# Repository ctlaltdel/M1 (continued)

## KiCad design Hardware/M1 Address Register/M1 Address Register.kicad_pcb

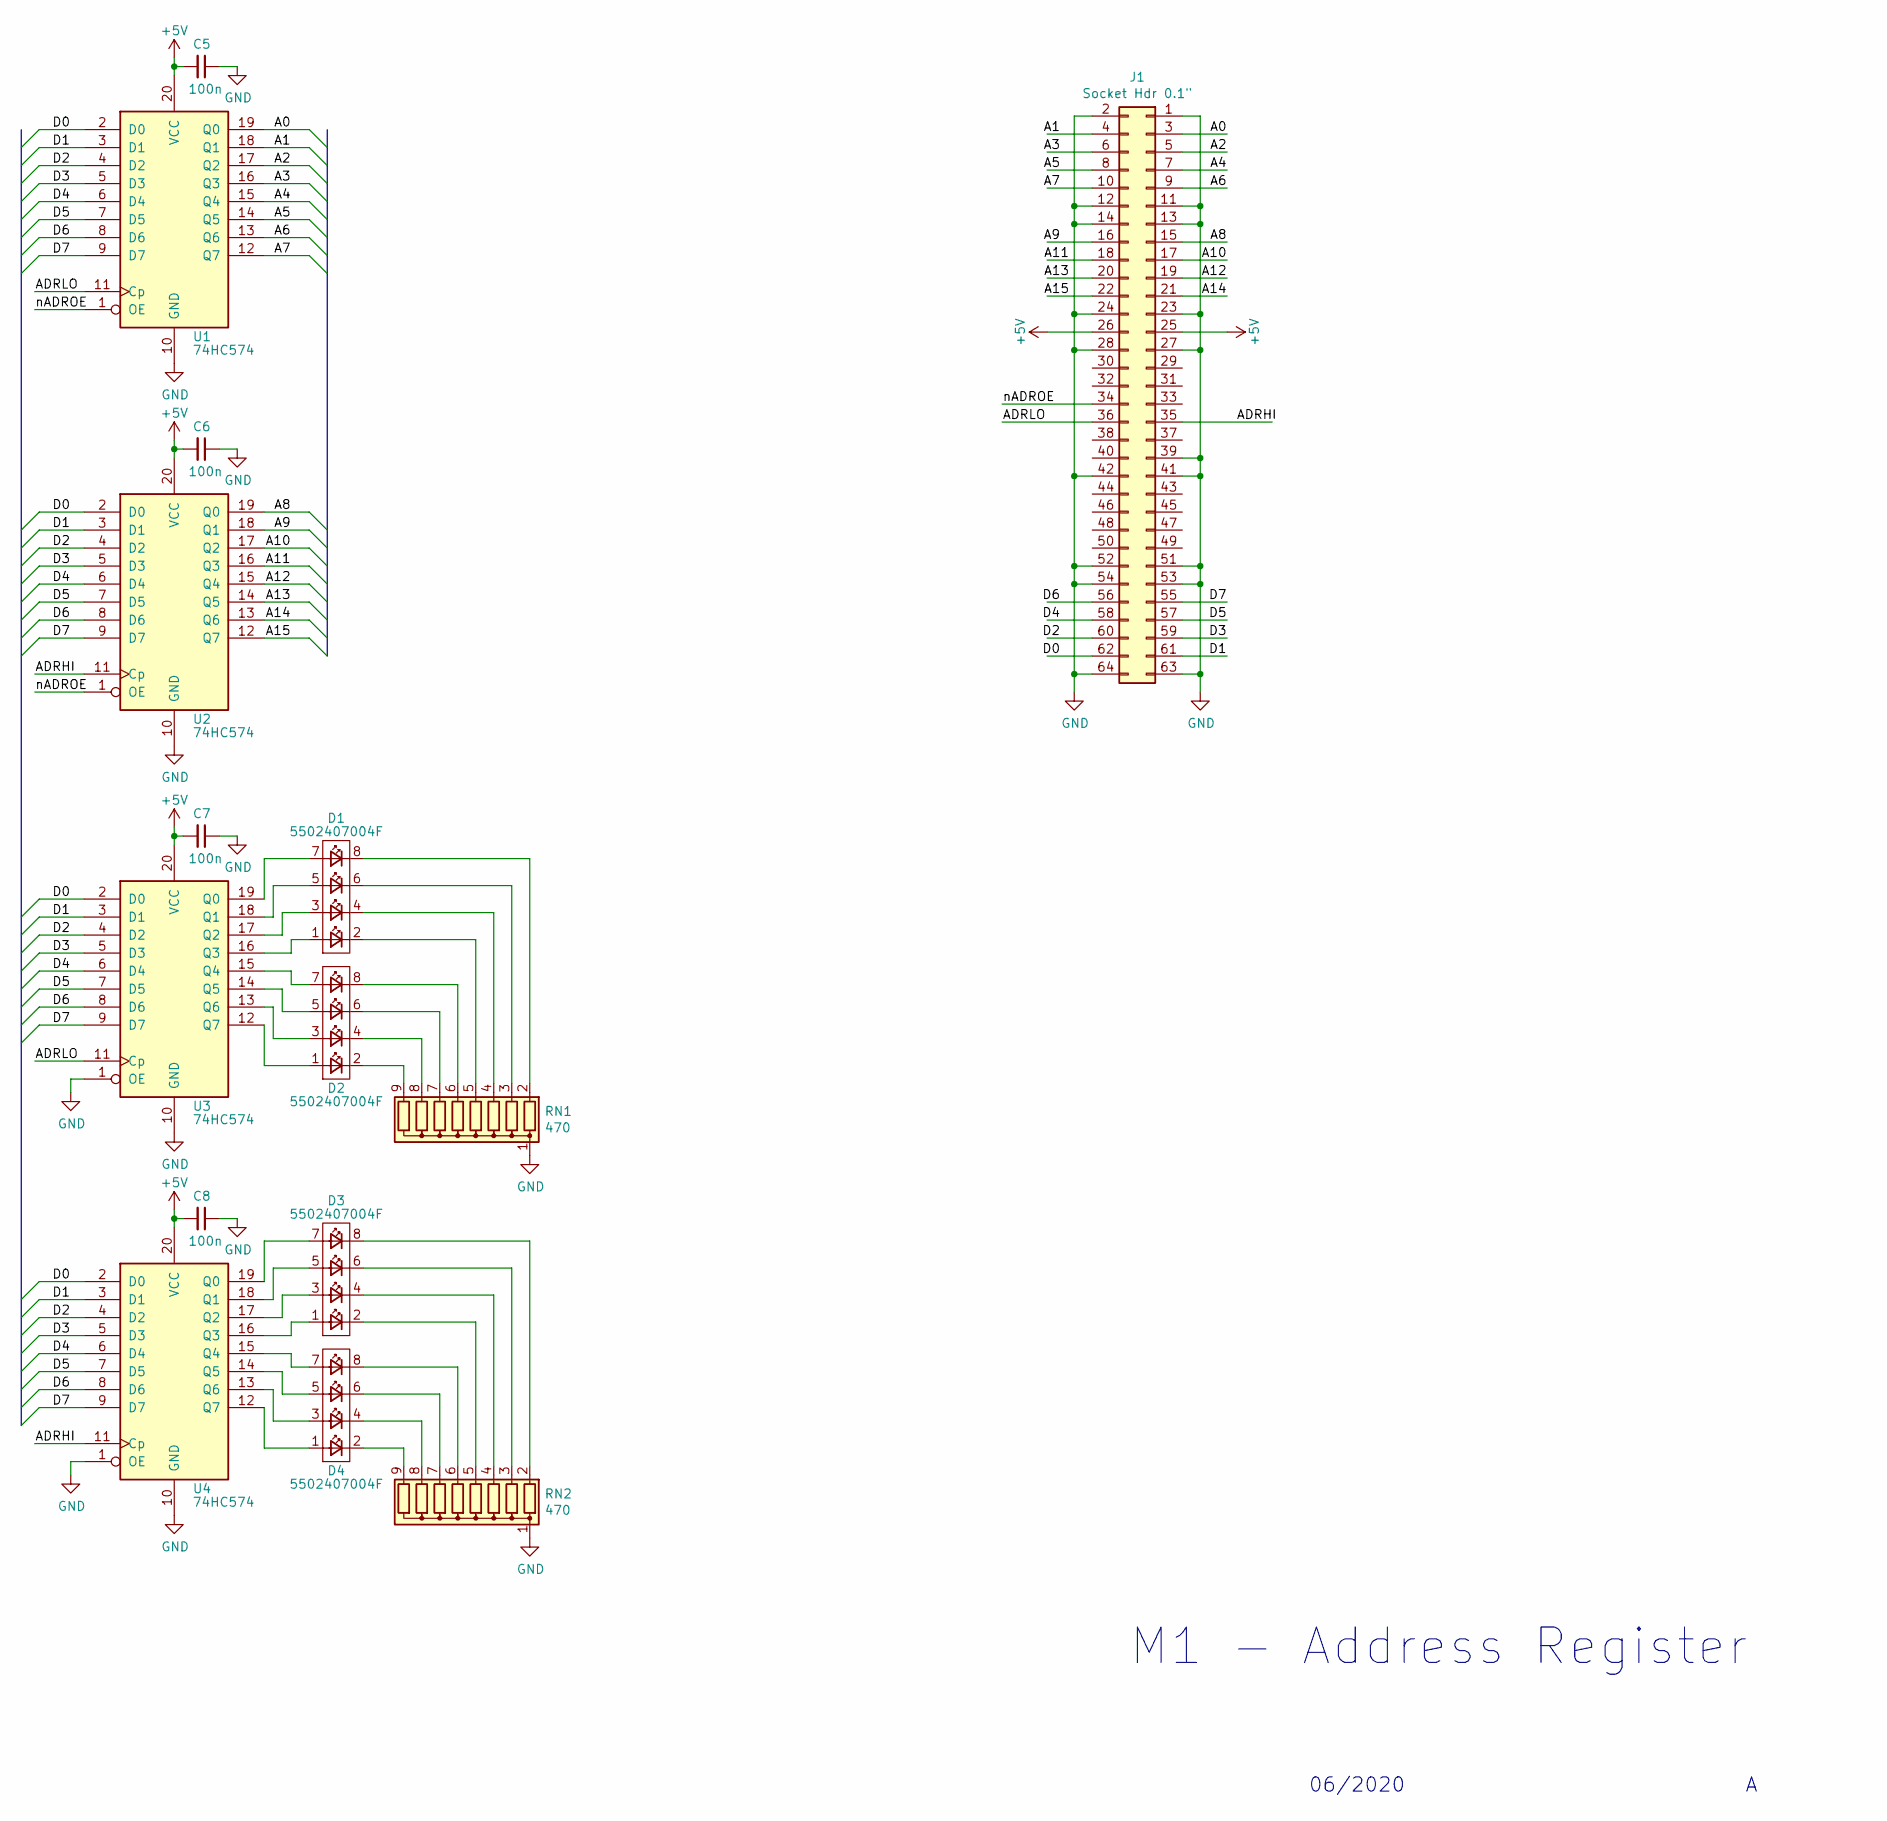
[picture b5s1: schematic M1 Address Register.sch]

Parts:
C5, C6, C7, C8: 100n; C_Disc_D5.1mm_W3.2mm_P5.00mm
D1, D2, D3, D4: 5502407004F
J1: Socket Hdr 0.1\"; IDC-Header_2x32_P2.54mm_Horizontal
RN1, RN2: 470; R_Array_SIP9
U1, U2, U3, U4: 74HC574; DIP-20_W7.62mm_Socket

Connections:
+5V: C5.2, C6.2, C7.2, C8.2, J1.25, J1.26, U1.20 (VCC), U2.20 (VCC), U3.20 (VCC), U4.20 (VCC)
/A0: J1.3, U1.19 (Q0)
/A1: J1.4, U1.18 (Q1)
/A2: J1.5, U1.17 (Q2)
/A3: J1.6, U1.16 (Q3)
/A4: J1.7, U1.15 (Q4)
/A5: J1.8, U1.14 (Q5)
/A6: J1.9, U1.13 (Q6)
/A7: J1.10, U1.12 (Q7)
/A8: J1.15, U2.19 (Q0)
/A9: J1.16, U2.18 (Q1)
/A10: J1.17, U2.17 (Q2)
/A11: J1.18, U2.16 (Q3)
/A12: J1.19, U2.15 (Q4)
/A13: J1.20, U2.14 (Q5)
/A14: J1.21, U2.13 (Q6)
/A15: J1.22, U2.12 (Q7)
/ADRHI: J1.35, U2.11 (Cp), U4.11 (Cp)
/ADRLO: J1.36, U1.11 (Cp), U3.11 (Cp)
/D0: J1.62, U1.2 (D0), U2.2 (D0), U3.2 (D0), U4.2 (D0)
/D1: J1.61, U1.3 (D1), U2.3 (D1), U3.3 (D1), U4.3 (D1)
/D2: J1.60, U1.4 (D2), U2.4 (D2), U3.4 (D2), U4.4 (D2)
/D3: J1.59, U1.5 (D3), U2.5 (D3), U3.5 (D3), U4.5 (D3)
/D4: J1.58, U1.6 (D4), U2.6 (D4), U3.6 (D4), U4.6 (D4)
/D5: J1.57, U1.7 (D5), U2.7 (D5), U3.7 (D5), U4.7 (D5)
/D6: J1.56, U1.8 (D6), U2.8 (D6), U3.8 (D6), U4.8 (D6)
/D7: J1.55, U1.9 (D7), U2.9 (D7), U3.9 (D7), U4.9 (D7)
/nADROE: J1.34, U1.1 (OE), U2.1 (OE)
GND: C5.1, C6.1, C7.1, C8.1, J1.1, J1.2, J1.11, J1.12, J1.13, J1.14, J1.23, J1.24, J1.27, J1.28, J1.39, J1.41, J1.42, J1.51, J1.52, J1.53, J1.54, J1.63, J1.64, RN1.1 (common), RN2.1 (common), U1.10 (GND), U2.10 (GND), U3.1 (OE), U3.10 (GND), U4.1 (OE), U4.10 (GND)
unnamed: D1.1, U3.16 (Q3)
unnamed: D1.2, RN1.5 (R4)
unnamed: D1.3, U3.17 (Q2)
unnamed: D1.4, RN1.4 (R3)
unnamed: D1.5, U3.18 (Q1)
unnamed: D1.6, RN1.3 (R2)
unnamed: D1.7, U3.19 (Q0)
unnamed: D1.8, RN1.2 (R1)
unnamed: D2.1, U3.12 (Q7)
unnamed: D2.2, RN1.9 (R8)
unnamed: D2.3, U3.13 (Q6)
unnamed: D2.4, RN1.8 (R7)
unnamed: D2.5, U3.14 (Q5)
unnamed: D2.6, RN1.7 (R6)
unnamed: D2.7, U3.15 (Q4)
unnamed: D2.8, RN1.6 (R5)
unnamed: D3.1, U4.16 (Q3)
unnamed: D3.2, RN2.5 (R4)
unnamed: D3.3, U4.17 (Q2)
unnamed: D3.4, RN2.4 (R3)
unnamed: D3.5, U4.18 (Q1)
unnamed: D3.6, RN2.3 (R2)
unnamed: D3.7, U4.19 (Q0)
unnamed: D3.8, RN2.2 (R1)
unnamed: D4.1, U4.12 (Q7)
unnamed: D4.2, RN2.9 (R8)
unnamed: D4.3, U4.13 (Q6)
unnamed: D4.4, RN2.8 (R7)
unnamed: D4.5, U4.14 (Q5)
unnamed: D4.6, RN2.7 (R6)
unnamed: D4.7, U4.15 (Q4)
unnamed: D4.8, RN2.6 (R5)

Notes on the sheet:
M1 - Address Register
06/2020

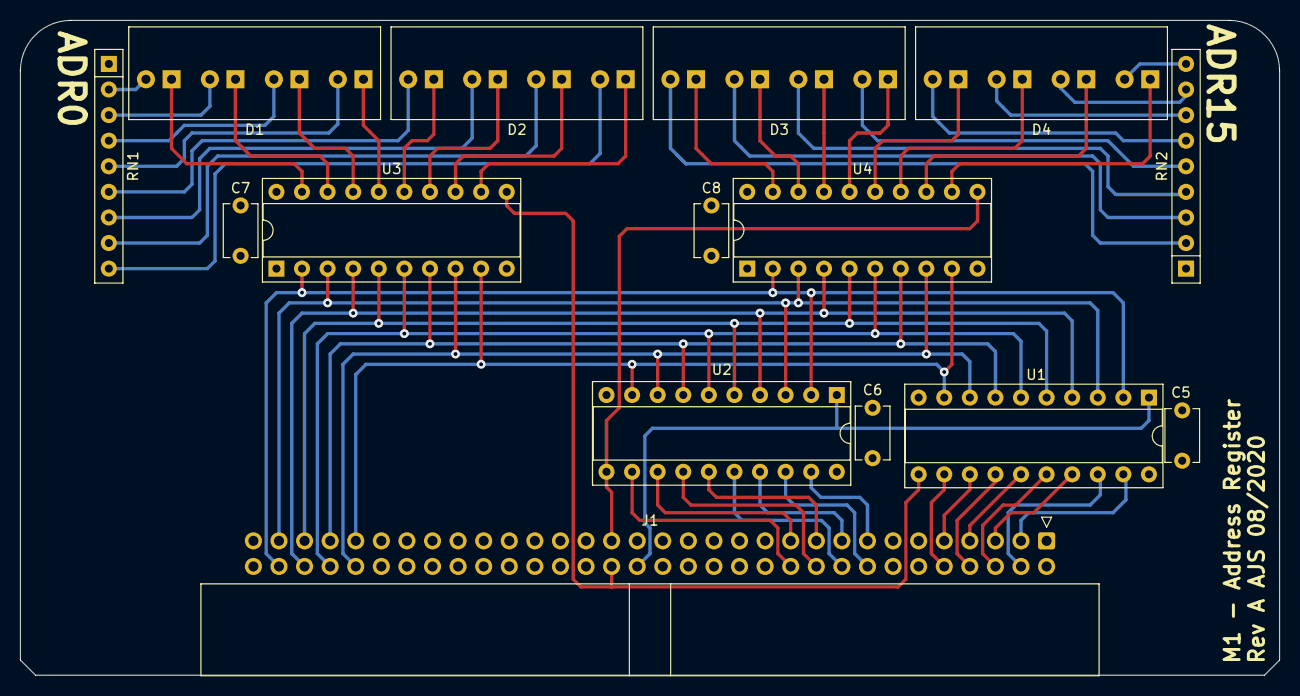
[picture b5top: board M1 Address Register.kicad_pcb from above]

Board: 4 copper layers, 125.0 x 65.0 mm, 15 parts (0 on the bottom side), 61 nets.

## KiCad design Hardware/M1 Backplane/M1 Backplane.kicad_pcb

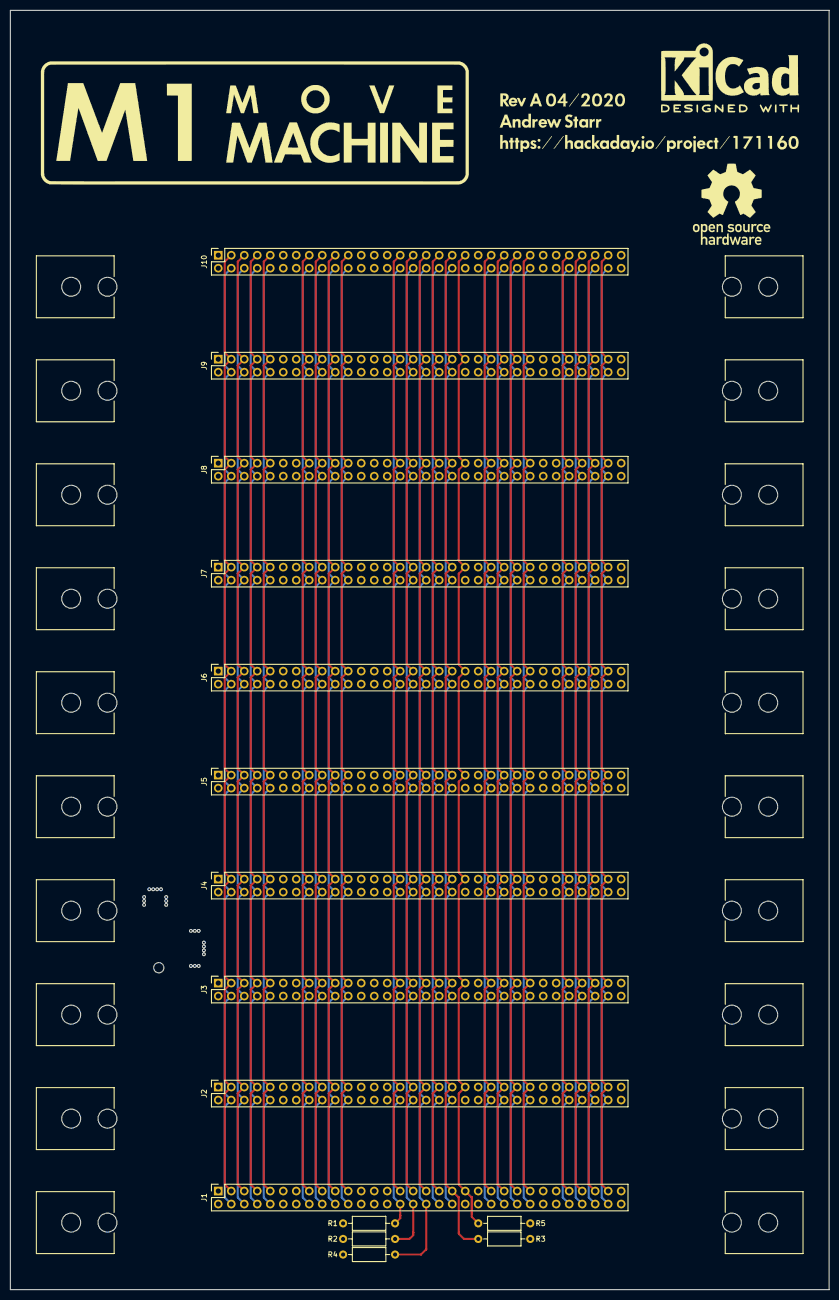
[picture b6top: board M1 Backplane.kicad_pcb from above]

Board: 4 copper layers, 160.0 x 250.0 mm, 36 parts (1 on the bottom side), 45 nets.

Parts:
J1, J2, J3, J4, J5, J6, J7, J8, J9, J10: Socket Hdr 0.1"; PinSocket_2x32_P2.54mm_Vertical
J11, J12, J13, J14, J15, J16, J17, J18, J19, J20, J21, J22, J23, J24, J25, J26, J27, J28, J29, J30: CARD_GUIDE; VG2
J31: PJ-036AH; BarrelJack_CUI_PJ-036AH-SMT_Horizontal
R1, R2, R3, R4, R5: 10k; R_Axial_DIN0207_L6.3mm_D2.5mm_P10.16mm_Horizontal

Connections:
+5V: J1.25, J1.26, J2.25, J2.26, J3.25, J3.26, J4.25, J4.26, J5.25, J5.26, J6.25, J6.26, J7.25, J7.26, J8.25, J8.26, J9.25, J9.26, J10.25, J10.26, J31.1, R1.1, R2.1, R3.1, R4.1, R5.1
/A0: J1.3, J2.3, J3.3, J4.3, J5.3, J6.3, J7.3, J8.3, J9.3, J10.3
/A1: J1.4, J2.4, J3.4, J4.4, J5.4, J6.4, J7.4, J8.4, J9.4, J10.4
/A2: J1.5, J2.5, J3.5, J4.5, J5.5, J6.5, J7.5, J8.5, J9.5, J10.5
/A3: J1.6, J2.6, J3.6, J4.6, J5.6, J6.6, J7.6, J8.6, J9.6, J10.6
/A4: J1.7, J2.7, J3.7, J4.7, J5.7, J6.7, J7.7, J8.7, J9.7, J10.7
/A5: J1.8, J2.8, J3.8, J4.8, J5.8, J6.8, J7.8, J8.8, J9.8, J10.8
/A6: J1.9, J2.9, J3.9, J4.9, J5.9, J6.9, J7.9, J8.9, J9.9, J10.9
/A7: J1.10, J2.10, J3.10, J4.10, J5.10, J6.10, J7.10, J8.10, J9.10, J10.10
/A8: J1.15, J2.15, J3.15, J4.15, J5.15, J6.15, J7.15, J8.15, J9.15, J10.15
/A9: J1.16, J2.16, J3.16, J4.16, J5.16, J6.16, J7.16, J8.16, J9.16, J10.16
/A10: J1.17, J2.17, J3.17, J4.17, J5.17, J6.17, J7.17, J8.17, J9.17, J10.17
/A11: J1.18, J2.18, J3.18, J4.18, J5.18, J6.18, J7.18, J8.18, J9.18, J10.18
/A12: J1.19, J2.19, J3.19, J4.19, J5.19, J6.19, J7.19, J8.19, J9.19, J10.19
/A13: J1.20, J2.20, J3.20, J4.20, J5.20, J6.20, J7.20, J8.20, J9.20, J10.20
/A14: J1.21, J2.21, J3.21, J4.21, J5.21, J6.21, J7.21, J8.21, J9.21, J10.21
/A15: J1.22, J2.22, J3.22, J4.22, J5.22, J6.22, J7.22, J8.22, J9.22, J10.22
/ADRHI: J1.35, J2.35, J3.35, J4.35, J5.35, J6.35, J7.35, J8.35, J9.35, J10.35
/D0: J1.62, J2.62, J3.62, J4.62, J5.62, J6.62, J7.62, J8.62, J9.62, J10.62
/D1: J1.61, J2.61, J3.61, J4.61, J5.61, J6.61, J7.61, J8.61, J9.61, J10.61
/D2: J1.60, J2.60, J3.60, J4.60, J5.60, J6.60, J7.60, J8.60, J9.60, J10.60
/D3: J1.59, J2.59, J3.59, J4.59, J5.59, J6.59, J7.59, J8.59, J9.59, J10.59
/D4: J1.58, J2.58, J3.58, J4.58, J5.58, J6.58, J7.58, J8.58, J9.58, J10.58
/D5: J1.57, J2.57, J3.57, J4.57, J5.57, J6.57, J7.57, J8.57, J9.57, J10.57
/D6: J1.56, J2.56, J3.56, J4.56, J5.56, J6.56, J7.56, J8.56, J9.56, J10.56
/D7: J1.55, J2.55, J3.55, J4.55, J5.55, J6.55, J7.55, J8.55, J9.55, J10.55
/PCINC: J1.31, J2.31, J3.31, J4.31, J5.31, J6.31, J7.31, J8.31, J9.31, J10.31
/TMPLD: J1.33, J2.33, J3.33, J4.33, J5.33, J6.33, J7.33, J8.33, J9.33, J10.33
/nADRLO: J1.36, J2.36, J3.36, J4.36, J5.36, J6.36, J7.36, J8.36, J9.36, J10.36
/nADROE: J1.34, J2.34, J3.34, J4.34, J5.34, J6.34, J7.34, J8.34, J9.34, J10.34, R4.2
/nINT: J1.38, J2.38, J3.38, J4.38, J5.38, J6.38, J7.38, J8.38, J9.38, J10.38
/nIOSEL0: J1.43, J2.43, J3.43, J4.43, J5.43, J6.43, J7.43, J8.43, J9.43, J10.43
/nIOSEL1: J1.44, J2.44, J3.44, J4.44, J5.44, J6.44, J7.44, J8.44, J9.44, J10.44
/nIOSEL2: J1.45, J2.45, J3.45, J4.45, J5.45, J6.45, J7.45, J8.45, J9.45, J10.45
/nIOSEL3: J1.46, J2.46, J3.46, J4.46, J5.46, J6.46, J7.46, J8.46, J9.46, J10.46
/nIOSEL4: J1.47, J2.47, J3.47, J4.47, J5.47, J6.47, J7.47, J8.47, J9.47, J10.47
/nIOSEL5: J1.48, J2.48, J3.48, J4.48, J5.48, J6.48, J7.48, J8.48, J9.48, J10.48
/nIOSEL6: J1.49, J2.49, J3.49, J4.49, J5.49, J6.49, J7.49, J8.49, J9.49, J10.49
/nIOSEL7: J1.50, J2.50, J3.50, J4.50, J5.50, J6.50, J7.50, J8.50, J9.50, J10.50
/nMEN: J1.39, J2.39, J3.39, J4.39, J5.39, J6.39, J7.39, J8.39, J9.39, J10.39, R5.2
/nPCOE: J1.30, J2.30, J3.30, J4.30, J5.30, J6.30, J7.30, J8.30, J9.30, J10.30, R1.2
/nSYSRST: J1.37, J2.37, J3.37, J4.37, J5.37, J6.37, J7.37, J8.37, J9.37, J10.37, R3.2
/nTMPOE: J1.32, J2.32, J3.32, J4.32, J5.32, J6.32, J7.32, J8.32, J9.32, J10.32, R2.2
/nWR: J1.29, J2.29, J3.29, J4.29, J5.29, J6.29, J7.29, J8.29, J9.29, J10.29
GND: J1.1, J1.2, J1.11, J1.12, J1.13, J1.14, J1.23, J1.24, J1.27, J1.28, J1.40, J1.41, J1.42, J1.51, J1.52, J1.53, J1.54, J1.63, J1.64, J2.1, J2.2, J2.11, J2.12, J2.13, J2.14, J2.23, J2.24, J2.27, J2.28, J2.40, J2.41, J2.42, J2.51, J2.52, J2.53, J2.54, J2.63, J2.64, J3.1, J3.2, J3.11, J3.12, J3.13, J3.14, J3.23, J3.24, J3.27, J3.28, J3.40, J3.41, J3.42, J3.51, J3.52, J3.53, J3.54, J3.63, J3.64, J4.1, J4.2, J4.11, J4.12, J4.13, J4.14, J4.23, J4.24, J4.27, J4.28, J4.40, J4.41, J4.42, J4.51, J4.52, J4.53, J4.54, J4.63, J4.64, J5.1, J5.2, J5.11, J5.12, J5.13, J5.14, J5.23, J5.24, J5.27, J5.28, J5.40, J5.41, J5.42, J5.51, J5.52, J5.53, J5.54, J5.63, J5.64, J6.1, J6.2, J6.11, J6.12, J6.13, J6.14, J6.23, J6.24, J6.27, J6.28, J6.40, J6.41, J6.42, J6.51, J6.52, J6.53, J6.54, J6.63, J6.64, J7.1, J7.2, J7.11, J7.12, J7.13, J7.14, J7.23, J7.24, J7.27, J7.28, J7.40, J7.41, J7.42, J7.51, J7.52, J7.53, J7.54, J7.63, J7.64, J8.1, J8.2, J8.11, J8.12, J8.13, J8.14, J8.23, J8.24, J8.27, J8.28, J8.40, J8.41, J8.42, J8.51, J8.52, J8.53, J8.54, J8.63, J8.64, J9.1, J9.2, J9.11, J9.12, J9.13, J9.14, J9.23, J9.24, J9.27, J9.28, J9.40, J9.41, J9.42, J9.51, J9.52, J9.53, J9.54, J9.63, J9.64, J10.1, J10.2, J10.11, J10.12, J10.13, J10.14, J10.23, J10.24, J10.27, J10.28, J10.40, J10.41, J10.42, J10.51, J10.52, J10.53, J10.54, J10.63, J10.64, J31.2

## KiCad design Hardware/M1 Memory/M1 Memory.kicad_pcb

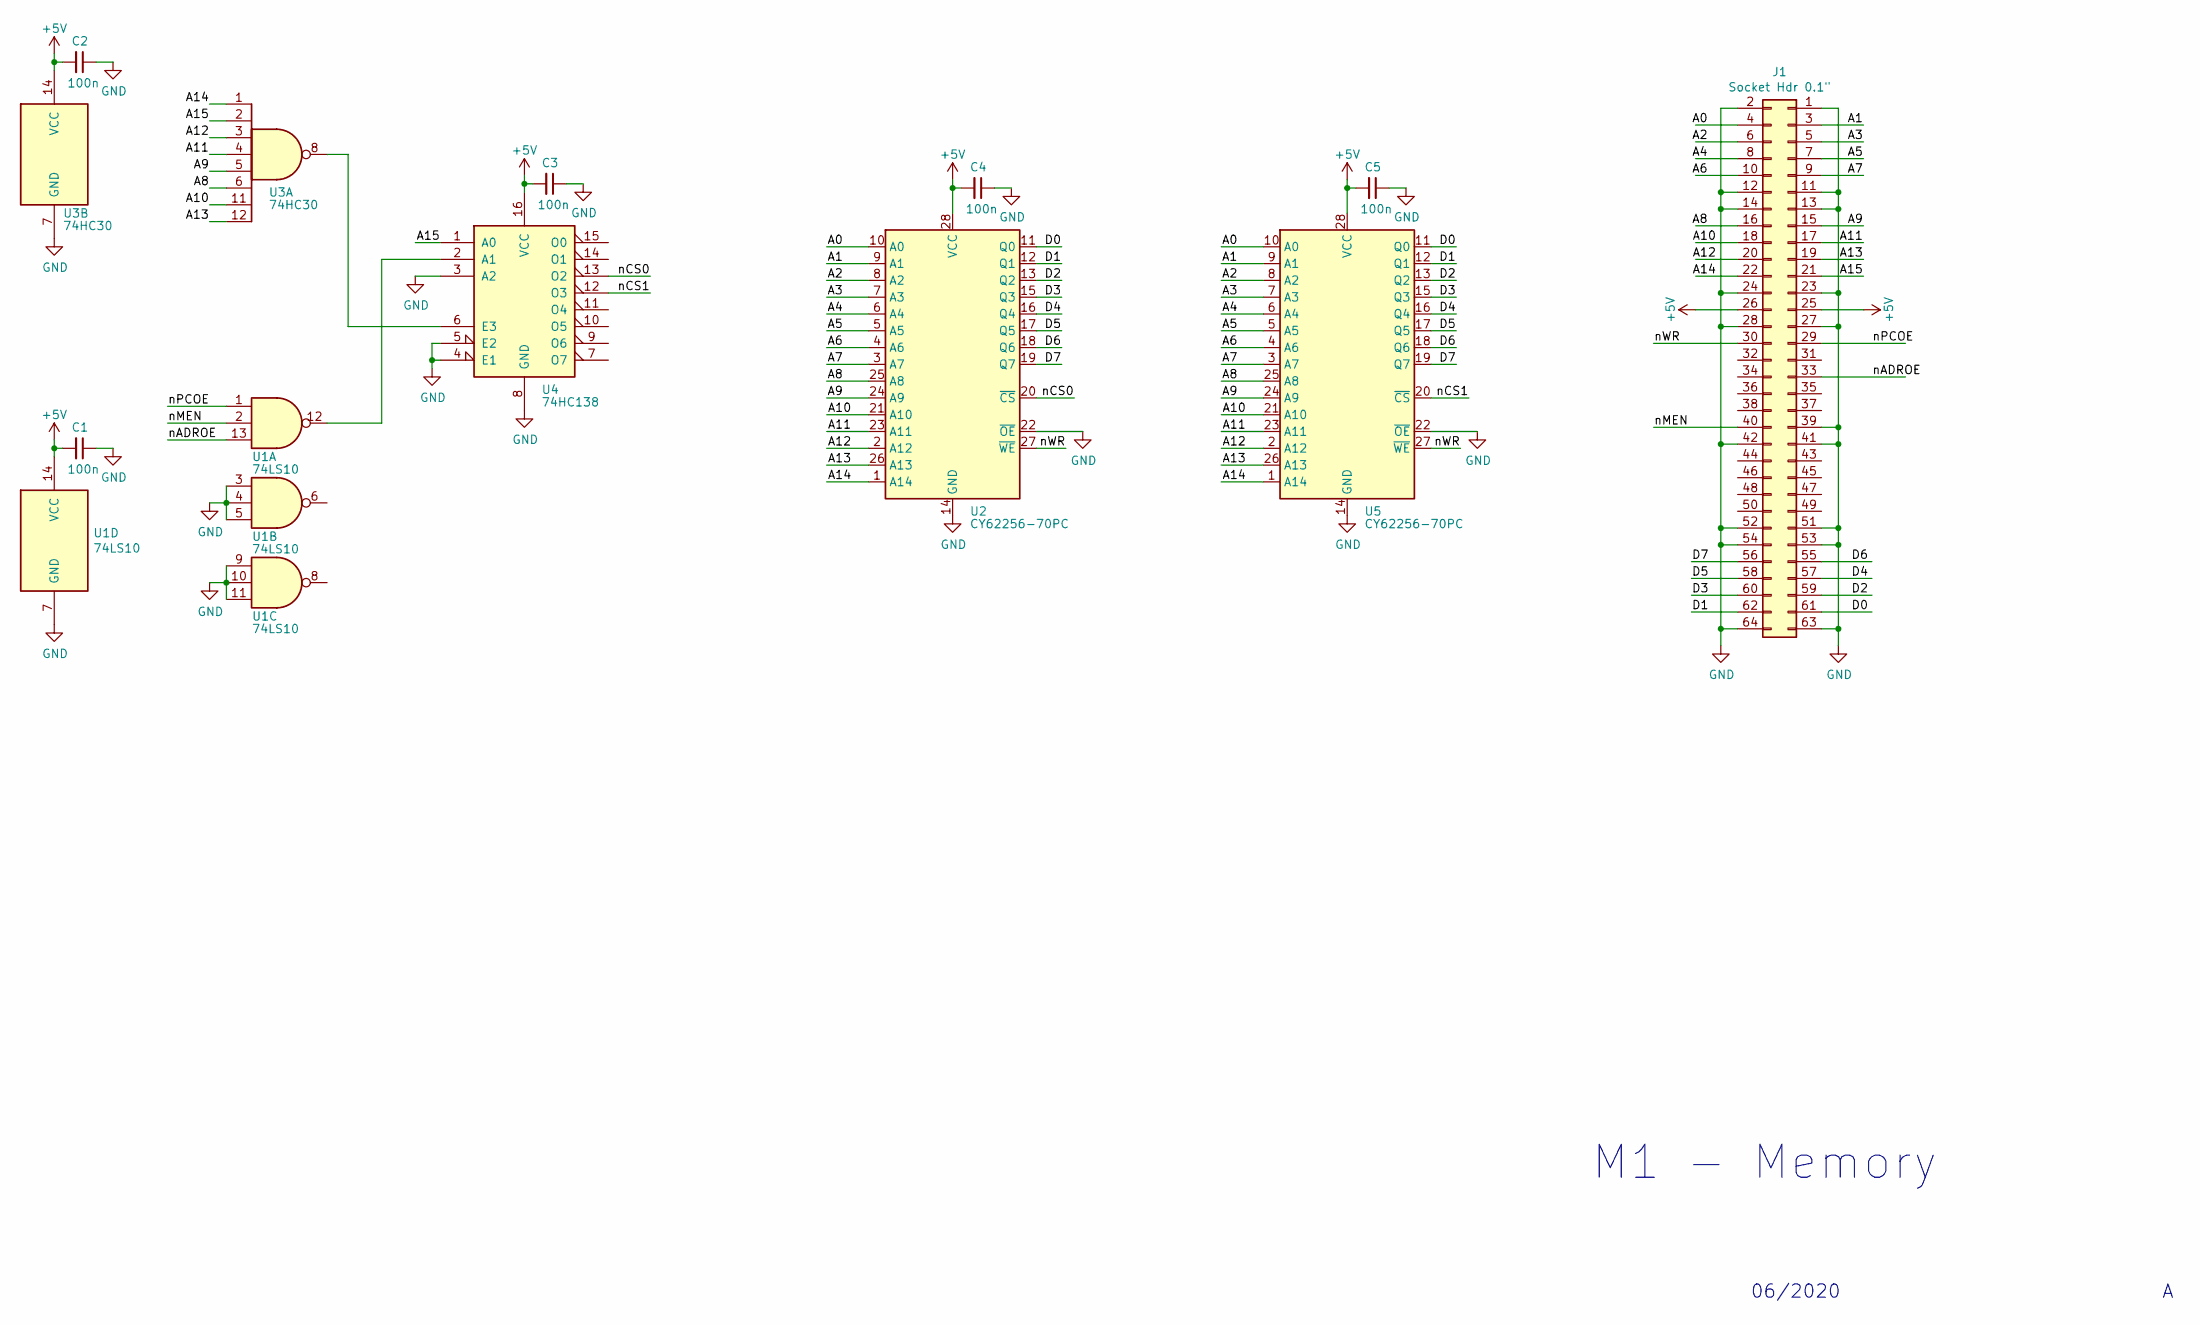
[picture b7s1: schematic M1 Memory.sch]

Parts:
C1, C2, C3, C4, C5: 100n; C_Disc_D5.1mm_W3.2mm_P5.00mm
J1: Socket Hdr 0.1\"; IDC-Header_2x32_P2.54mm_Horizontal
U1: 74LS10; DIP-14_W7.62mm_Socket
U2, U5: CY62256-70PC; DIP-28_W7.62mm_Socket
U3: 74HC30; DIP-14_W7.62mm_Socket
U4: 74HC138; DIP-16_W7.62mm_Socket

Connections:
+5V: C1.2, C2.2, C3.2, C4.2, C5.2, J1.25, J1.26, U1.14 (VCC), U2.28 (VCC), U3.14 (VCC), U4.16 (VCC), U5.28 (VCC)
/A0: J1.4, U2.10 (A0), U5.10 (A0)
/A1: J1.3, U2.9 (A1), U5.9 (A1)
/A2: J1.6, U2.8 (A2), U5.8 (A2)
/A3: J1.5, U2.7 (A3), U5.7 (A3)
/A4: J1.8, U2.6 (A4), U5.6 (A4)
/A5: J1.7, U2.5 (A5), U5.5 (A5)
/A6: J1.10, U2.4 (A6), U5.4 (A6)
/A7: J1.9, U2.3 (A7), U5.3 (A7)
/A8: J1.16, U2.25 (A8), U3.6, U5.25 (A8)
/A9: J1.15, U2.24 (A9), U3.5, U5.24 (A9)
/A10: J1.18, U2.21 (A10), U3.11, U5.21 (A10)
/A11: J1.17, U2.23 (A11), U3.4, U5.23 (A11)
/A12: J1.20, U2.2 (A12), U3.3, U5.2 (A12)
/A13: J1.19, U2.26 (A13), U3.12, U5.26 (A13)
/A14: J1.22, U2.1 (A14), U3.1, U5.1 (A14)
/A15: J1.21, U3.2, U4.1 (A0)
/D0: J1.61, U2.11 (Q0), U5.11 (Q0)
/D1: J1.62, U2.12 (Q1), U5.12 (Q1)
/D2: J1.59, U2.13 (Q2), U5.13 (Q2)
/D3: J1.60, U2.15 (Q3), U5.15 (Q3)
/D4: J1.57, U2.16 (Q4), U5.16 (Q4)
/D5: J1.58, U2.17 (Q5), U5.17 (Q5)
/D6: J1.55, U2.18 (Q6), U5.18 (Q6)
/D7: J1.56, U2.19 (Q7), U5.19 (Q7)
/nADROE: J1.33, U1.13
/nCS0: U2.20 (~CS), U4.13 (O2)
/nCS1: U4.12 (O3), U5.20 (~CS)
/nMEN: J1.40, U1.2
/nPCOE: J1.29, U1.1
/nWR: J1.30, U2.27 (~WE), U5.27 (~WE)
GND: C1.1, C2.1, C3.1, C4.1, C5.1, J1.1, J1.2, J1.11, J1.12, J1.13, J1.14, J1.23, J1.24, J1.27, J1.28, J1.39, J1.41, J1.42, J1.51, J1.52, J1.53, J1.54, J1.63, J1.64, U1.3, U1.4, U1.5, U1.7 (GND), U1.9, U1.10, U1.11, U2.14 (GND), U2.22 (~OE), U3.7 (GND), U4.3 (A2), U4.4 (E1), U4.5 (E2), U4.8 (GND), U5.14 (GND), U5.22 (~OE)
unnamed: U1.12, U4.2 (A1)
unnamed: U3.8, U4.6 (E3)

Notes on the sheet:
M1 - Memory
06/2020

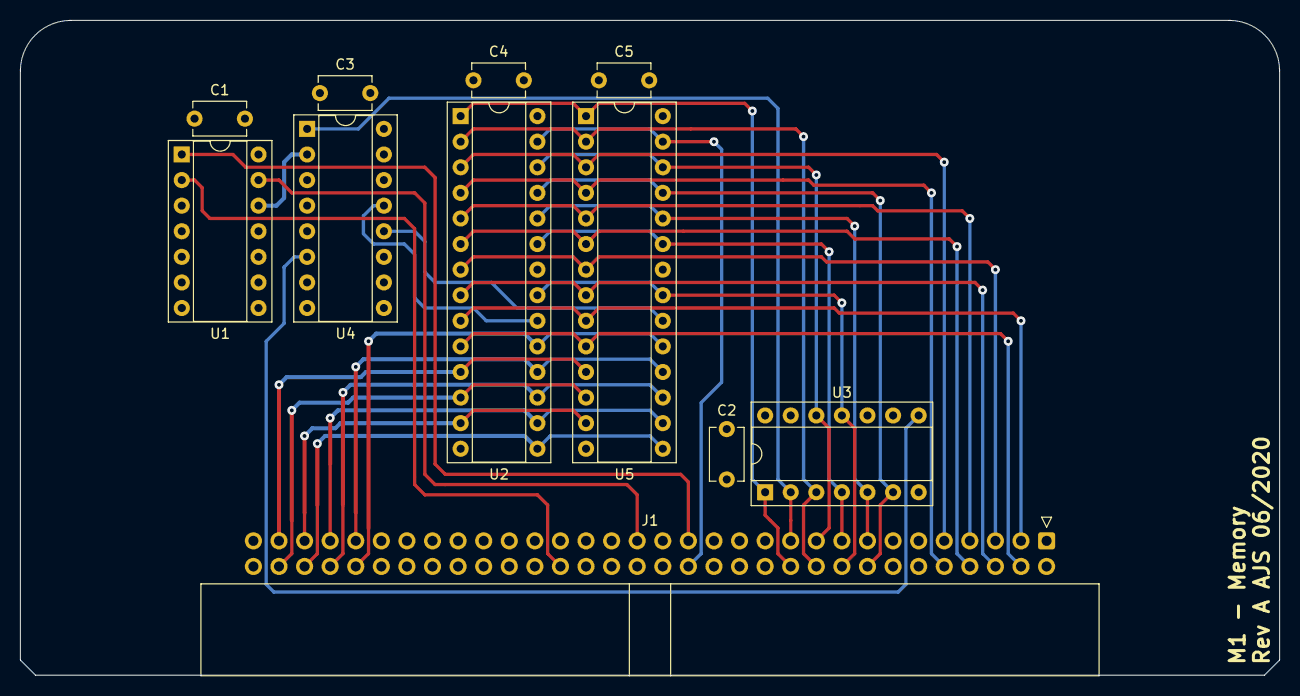
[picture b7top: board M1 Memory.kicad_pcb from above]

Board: 4 copper layers, 125.0 x 65.0 mm, 11 parts (0 on the bottom side), 34 nets.

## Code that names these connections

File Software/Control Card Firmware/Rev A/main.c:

/*
 * main.c
 *
 *  Created on: 2/06/2020
 *      Author: ajs
 */
#define F_CPU 16000000UL

#define M1_ADDR_HI	PORTF
#define M1_ADDR_LO	PORTA
#define M1_PCRST	PC5
#define M1_PCINC	PC4
#define M1_ADRHI	PG0
#define M1_ADRLO	PC0
#define BUS_OUTPUT 1
#define BUS_INPUT 0

#include <stdio.h>
#include <avr/io.h>
#include <util/delay.h>
#include <avr/interrupt.h>
#include <stdbool.h>
#include <avr/cpufunc.h>
//#include <uart.h>

extern unsigned char bc[];

void usart_init(uint16_t ubrr);
char usart_getchar( void );
void usart_putchar( char data );
void usart_pstr (char *s);
unsigned char usart_kbhit(void);
int usart_putchar_printf(char var, FILE *stream);
static FILE mystdout = FDEV_SETUP_STREAM(usart_putchar_printf, NULL, _FDEV_SETUP_WRITE);
void set_address_bus_mode(int mode);
void set_data_bus_mode(int mode);
void set_address_bus_value(unsigned int value);
void set_data_bus_value(unsigned char value);
void load_address_hi_register(unsigned int value);
void load_address_lo_register(unsigned int value);
void load_address_register(unsigned int value);
void load_temp_register(unsigned int value);
void init(void);
void reset(void);
void incr_pc(void);
void set_temp_register_output(void);
void set_temp_register_hi_z(void);

int main(void) {
	unsigned int i=0, j;

    stdout = &mystdout;
    usart_init (0);
    printf("Hello world!\n");

	init();
	load_temp_register(0x0);

	for(j=0; j<=0x5500; j++)
	{
		load_address_register(i);
		load_temp_register(~(i>>8));
		incr_pc();
		i++;
//		_delay_ms(2);
	}

	set_temp_register_output();
	PORTC &= ~(1<<PC0);
	_NOP();
	_NOP();
	PORTC |= 1<<PC0;
	set_temp_register_hi_z();

//    UCSRB |= (1 << RXCIE); // Enable the USART Receive Complete interrupt (USART_RXC)
//    sei(); // Enable the Global Interrupt Enable flag so that interrupts can be processed

    return 0;
}

void init(void)
{
    DDRB = 0xff;
    DDRC = 0xff;
    DDRG = 0xff;

    PORTC |= 1<<PC7;	// deassert nPCOE
    PORTC |= 1<<PC3;	// deassert nADROE
    PORTC |= 1<<PC5;	// deassert nTMPOE

	reset();
}

void reset(void)
{
    PORTG &= ~(1<<PG1);
    PORTG |= 1<<PG1;
}

void incr_pc(void)
{
	PORTC &= ~(1<<PC4);
	_NOP();
	_NOP();
	PORTC |= 1<<PC4;
}

void set_address_bus_mode(int mode)
{
	if(mode==BUS_OUTPUT)
	{
		DDRF = 0xff;
		DDRA = 0xff;
	}
	else
	{
		DDRF = 0x00;
		DDRA = 0x00;
	}
}

void set_data_bus_mode(int mode)
{
	if(mode==BUS_OUTPUT)
	{
		DDRD = 0xff;
	}
	else
	{
		DDRD = 0x00;
	}
}

void set_address_bus_value(unsigned int value)
{
   PORTF = bc[(value & 0x00ff)];
	PORTA = bc[(value >> 8)]; 
}

void set_data_bus_value(unsigned char value)
{
	set_data_bus_mode(BUS_OUTPUT);
   PORTD = bc[value];
}

void load_address_hi_register(unsigned int value)
{
	set_data_bus_value(value);
	PORTC &= ~(1<<PC0);
	_NOP();
	_NOP();
	PORTC |= 1<<PC0;
}

void set_temp_register_output(void)
{
	PORTC &= ~(1<<PC5);
	_NOP();
	_NOP();
}

void set_temp_register_hi_z(void)
{
	PORTC |= 1<<PC5;
	_NOP();
	_NOP();
}

void load_address_lo_register(unsigned int value)
{
	set_data_bus_value(value);
	PORTC &= ~(1<<PC1);
	_NOP();
	_NOP();
	PORTC |= 1<<PC1;
}

void load_address_register(unsigned int value)
{
	load_address_lo_register(value & 0xff);
	load_address_hi_register(value >> 8);
}

void load_temp_register(unsigned int value)
{
	set_data_bus_value(value);
	PORTC &= ~(1<<PC2);
	_NOP();
	_NOP();
	PORTC |= 1<<PC2;
}

void usart_init( uint16_t ubrr) {
    // Set baud rate
    UBRRH = (uint8_t)(ubrr>>8);
    UBRRL = (uint8_t)ubrr;
    // Enable receiver and transmitter
    UCSRB = (1<<RXEN)|(1<<TXEN);
    // Set frame format: 8data, 1stop bit
    UCSRC = (1<<USBS)|(3<<UCSZ0);
}
void usart_putchar(char data) {
    // Wait for empty transmit buffer
    while ( !(UCSRA & (_BV(UDRE))) );
    // Start transmission
    UDR = data;
}
char usart_getchar(void) {
    // Wait for incoming data
    while ( !(UCSRA & (_BV(RXC))) );
    // Return the data
    return UDR;
}
unsigned char usart_kbhit(void) {
    //return nonzero if char waiting polled version
    unsigned char b;
    b=0;
    if(UCSRA & (1<<RXC)) b=1;
    return b;
}
void usart_pstr(char *s) {
    // loop through entire string
    while (*s) {
        usart_putchar(*s);
        s++;
    }
}

int usart_putchar_printf(char var, FILE *stream) {
    if (var == '\n') usart_putchar('\r');
    usart_putchar(var);
    return 0;
}

ISR(USART0_RX_vect)
{
   char ReceivedByte;
   ReceivedByte = UDR; // Fetch the received byte value into the variable "ByteReceived"
   UDR = ReceivedByte; // Echo back the received byte back to the computer
}

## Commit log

2020-09-13 initial commit of design and firmware files
2020-09-13 added Hardware/.gitignore
2020-09-13 fix .gitignore location
2020-09-13 remove Datasheets folder from M1 Backplane
2020-09-19 daily update
